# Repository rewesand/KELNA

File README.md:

# KELNA

> [!NOTE]
> **This project is under development.**

Low-frequency noise preamplifier hardware for precision voltage references and Zener diodes, designed for the **0.1–10 Hz** measurement window. Nominal midband gain is **11,400 V/V (≈81.1 dB)**. The prototype uses a split battery supply of **±6.8 to ±8.4 V** and a **high-impedance output load**.

## PCB routing

**Front copper** · [SVG](docs/images/copper-front.svg)

**Back copper** · Underside view with reference overlay · [SVG](docs/images/copper-back.svg)

## Using the input

For the BNC input (J1), set JP1 to **1–2 (INT)**. Select **PRE** before connecting a reference, with positive voltage on the centre pin and return on the shell.

| SW1 position | Signal path |
| --- | --- |
| **PRE — precharge** | Charges C1 (2,200 µF) through R1 (15 kΩ) while isolating the amplifier from the reference's DC step. |
| **MEAS — measure** | Bypasses R1 and AC-couples the reference noise to the amplifier through C1. R3 (10 kΩ) provides the bias return. |

With a low-impedance 7 V reference and a discharged C1, PRE initially draws **0.47 mA**. The nominal time constant is **33 s**. Ideally, C1 charges to within **0.5 mV** of the reference in about **5.3 min**. After switching to MEAS, check that the first stage has headroom at TP1 and that J3 has settled before recording. Return to PRE before changing the reference or powering down.

For an external selector, move the single JP1 shunt to **2–3 (EXT)** and feed J2. This path bypasses C1, SW1 and R3. The selector must provide its own AC coupling, input bias return and precharge.

## Two gain stages

1. **×2,000** — four AD8428 amplifiers in parallel, with the output taken from U1 and AC-coupled to the second stage. [Analog Devices circuit, Figure 1](https://www.analog.com/en/resources/analog-dialogue/articles/low-noise-inamp-nanovolt-sensitivity.html)
2. **×5.7** — OPA2140 non-inverting gain stage (1 kΩ and 4.7 kΩ), followed by a second-order **10 Hz** low-pass filter.

The nominal midband gain is **2,000 × 5.7 = 11,400 V/V**. The two AC couplings have nominal corners near 7 mHz with a low-impedance source on J1. Apply the 0.1 Hz lower limit when analysing the recording.

## Board and connectors

100 × 60 mm, two layers. Connect J3 to a high-impedance input. Power connector J21 uses **1 = +BAT, 2 = battery midpoint / GND, 3 = −BAT**.

## Design files

- [KiCad project](KELNA.kicad_pro), [schematic](KELNA.kicad_sch) and [PCB](KELNA.kicad_pcb)
- [Vector schematic PDF](docs/schematic.pdf)
- [Assembly and mechanical drawings](KELNA-placement.pdf)
- [Copper-layer PDF](KELNA-routing.pdf)
- [Bill of materials](KELNA-BOM.csv) and [DRC report](KELNA-DRC.rpt)
- [Revision 0.14 fabrication archive](fabrication/KELNA-rev0.14-fab.zip)

## Schematic

[Schematic SVG](docs/images/schematic.svg) · [Schematic PDF](docs/schematic.pdf)

Several local footprints use KiCad library land patterns with modified silkscreen or solder access. [KiCad library notice](third_party/KiCad-library-license.md).

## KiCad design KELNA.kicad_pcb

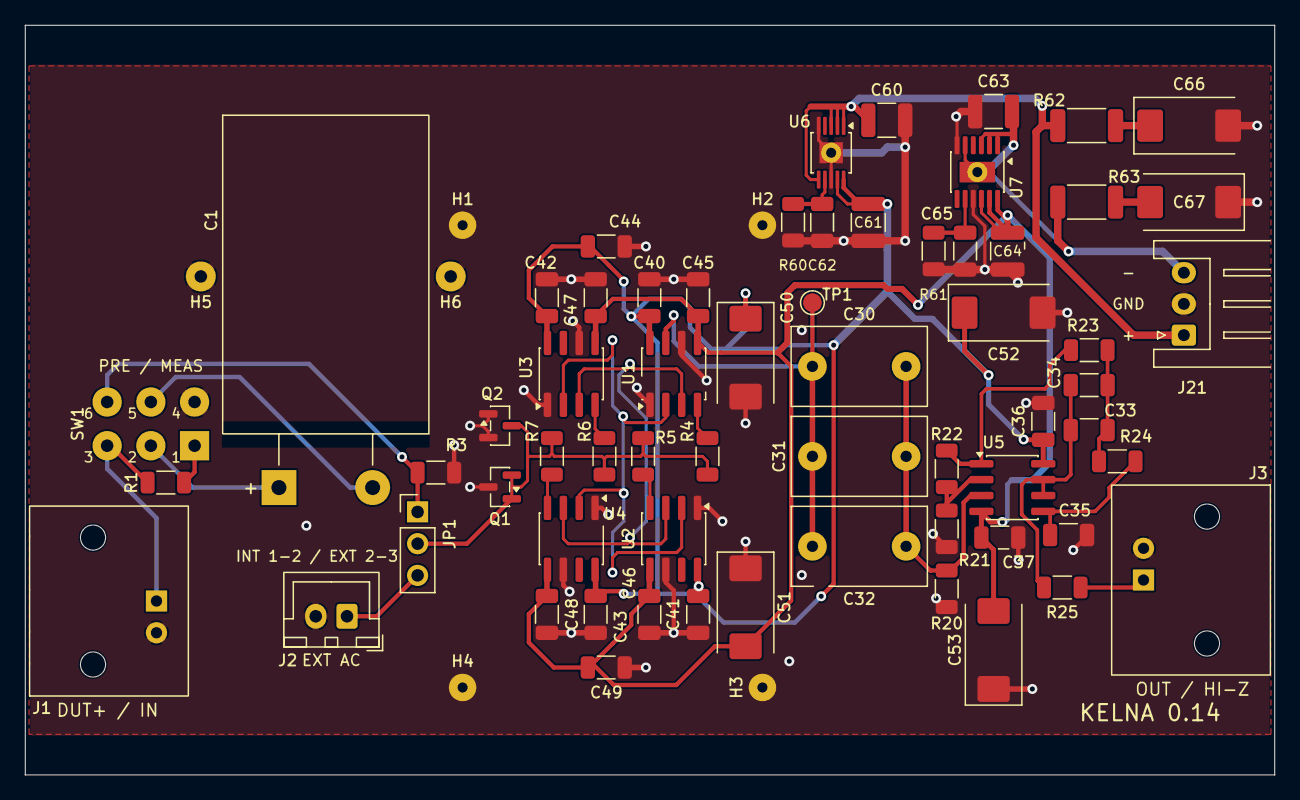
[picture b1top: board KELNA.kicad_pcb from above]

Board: 2 copper layers, 100.0 x 60.0 mm, 69 parts (0 on the bottom side), 30 nets.

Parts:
C1: 2200uF / 16V; CP_Radial_D16mm_L25mm_P7.50mm_Horizontal
C30, C31: 2.2u / 63V PET; C_KEMET_R66_L10.5mm_W6.0mm_P7.50mm
C32: 2.2u / 63V PET; C_KEMET_R66_L10.5mm_W6.0mm_P7.50mm_SilkTrim_C32
C33: 100n C0G; C_1206_3216Metric_SilkTrim_C33
C34, C36, C40, C41, C42, C43, C45, C46, C47, C48: 100n C0G; C_1206_3216Metric
C35: 100n C0G; C_1206_3216Metric_SilkTrim_C35
C37: 100n C0G; C_1206_3216Metric_SilkTrim_C37
C44, C49: 4.7 uF; C_1206_3216Metric
C50, C51, C52, C53, C66, C67: 47u / 16V; CP_EIA-7343-31_Kemet-D
C60, C61, C63: 22u / 25V; C_1210_3225Metric
C62, C65: 4.7u / 25V; C_1206_3216Metric
C64: 22u / 25V; C_1210_3225Metric_SilkTrim_C64
H1, H2, H3, H4: Shield GND; Shield_Post_PTH_D0.8mm
H5, H6: C1 clip GND; Clamp_Anchor_PTH_D1.0mm
J1: BNC DUT IN; BNC_TE_5227161-6_Horizontal
J2: EXT AC IN; JST_XH_B2B-XH-A_1x02_P2.50mm_Vertical
J3: BNC; BNC_TE_5227161-6_Horizontal
J21: BATTERY; JST_XH_S3B-XH-A_1x03_P2.50mm_Horizontal_Panel
JP1: INT / EXT; PinHeader_1x03_P2.54mm_Vertical
Q1, Q2: MMBF4117; SOT-23
R1: 15k; R_1206_3216Metric
R3: 10k; R_1206_3216Metric
R4, R5, R6, R7: 0R; R_1206_3216Metric
R20: 3.3M; R_1206_3216Metric
R21: 1k; R_1206_3216Metric
R22: 4.7k; R_1206_3216Metric
R23, R24: 113k; R_1206_3216Metric
R25: 2.2k; R_1206_3216Metric
R60, R61: 50.0k; R_1206_3216Metric
R62, R63: 0.47R; R_2010_5025Metric
SW1: PRE / MEAS; SW_DPDT_Panel_Wires_2x03_P3.5mm
TP1: PRE_OUT; TestPoint_Pad_D1.5mm
U1: AD8428BRZ; SOIC-8_3.9x4.9mm_P1.27mm_SilkTrim_U1
U2, U3: AD8428BRZ; SOIC-8_3.9x4.9mm_P1.27mm
U4: AD8428BRZ; SOIC-8_3.9x4.9mm_P1.27mm_SilkTrim_U4
U5: OPA2140; SOIC-8_3.9x4.9mm_P1.27mm
U6: LT3042IMSE; MSOP-10-1EP_3x3mm_P0.5mm_EP1.68x1.88mm_BacksideSolder
U7: LT3094EMSE; MSOP-12-1EP_3x4.039mm_P0.65mm_EP1.651x2.845mm_BacksideSolde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

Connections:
/+5VA: C36.1, C40.1, C41.1, C42.1, C43.1, C44.1, C50.1, C52.1, C61.1, U1.8 (V+), U2.8 (V+), U3.8 (V+), U4.8 (V+), U5.8 (V+), U6.9 (OUTS), U6.10 (OUT)
/-5VA: C37.1, C45.1, C46.1, C47.1, C48.1, C49.1, C51.2, C53.2, C64.1, U1.5 (V-), U2.5 (V-), U3.5 (V-), U4.5 (V-), U5.4 (V-), U7.10 (OUTS), U7.11 (OUT), U7.12 (OUT)
/AC_EXTERNAL: J2.1, JP1.3 (B)
/AC_INTERNAL: JP1.1 (A), R3.1, SW1.6 (C)
/DUT_IN: J1.1 (In), R1.1, SW1.3 (C)
/DUT_PRE: R1.2, SW1.1 (A)
/FIL_N: U1.2 (-FIL), U2.2 (-FIL), U3.2 (-FIL), U4.2 (-FIL)
/FIL_P: U1.3 (+FIL), U2.3 (+FIL), U3.3 (+FIL), U4.3 (+FIL)
/INPUT_PLUS: JP1.2 (C), Q1.1 (S), Q1.2 (D), Q2.3 (G), R4.1, R5.1, R6.1, R7.1
/OUT: J3.1 (In), R25.2
/POST_GAIN: R22.2, R23.1, U5.1
/PRE_OUT: C30.1, C31.1, C32.1, TP1.1 (1_1), U1.7 (OUT)
/VN_BAT: C63.1, J21.3, R63.1, U7.1 (IN), U7.2 (IN), U7.3 (EN/UV), U7.5 (PGFB), U7.13 (IN)
/VP_BAT: C60.1, J21.1, R62.1, U6.1 (IN), U6.2 (IN), U6.3 (EN/UV), U6.6 (PGFB)
GND: C35.2, C36.2, C37.2, C40.2, C41.2, C42.2, C43.2, C44.2, C45.2, C46.2, C47.2, C48.2, C49.2, C50.2, C51.1, C52.2, C53.1, C60.2, C61.2, C62.2, C63.2, C64.2, C65.2, C66.2, C67.1, H1.1 (1_1), H2.1 (1_1), H3.1 (1_1), H4.1 (1_1), H5.1 (1_1), H6.1 (1_1), J1.2 (Ext), J2.2, J3.2 (Ext), J21.2, Q1.3 (G), Q2.1 (S), Q2.2 (D), R3.2, R20.2, R21.2, R60.2, R61.2, SW1.4 (A), U1.1 (-IN), U1.6 (REF), U2.1 (-IN), U2.6 (REF), U3.1 (-IN), U3.6 (REF), U4.1 (-IN), U4.6 (REF), U6.5 (ILIM), U6.8 (GND), U6.11 (GND), U7.6 (ILIM), U7.9 (GND)
unnamed: C33.1, C34.1, R23.2, R24.1
unnamed: C66.1, R62.2
unnamed: C67.2, R63.2
unnamed: C1.1, SW1.2 (B)
unnamed: C1.2, SW1.5 (B)
unnamed: R4.2, U1.4 (+IN)
unnamed: R5.2, U2.4 (+IN)
unnamed: R6.2, U3.4 (+IN)
unnamed: R7.2, U4.4 (+IN)
unnamed: C30.2, C31.2, C32.2, R20.1, U5.3 (+)
unnamed: R21.1, R22.1, U5.2 (-)
unnamed: C35.1, R24.2, U5.5 (+)
unnamed: C33.2, C34.2, R25.1, U5.6 (-), U5.7
unnamed: C62.1, R60.1, U6.7 (SET)
unnamed: C65.1, R61.1, U7.8 (SET)

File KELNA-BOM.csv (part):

"Refs / Designator","Value / Description","Manufacturer","MPN","Mouser No","Qty per board or set","Qty to order","Assembly / Variant","Footprint","Mouser DE URL","Observed stock pcs","Stock source locale","Index age at 2026-11-20","Stock status","Stock evidence URL","Other indexed observations","Manufacturer URL","Notes / Примечания"
"C1","2200uF / 16V","Nichicon","UKL1C222MHD","647-UKL1C222MHD","1","1","Вход; электролит установлен лёжа","KELNA:CP_Radial_D16mm_L25mm_P7.50mm_Horizontal","https://www.mouser.de/ProductDetail/Nichicon/UKL1C222MHD","244","DE","crawled yesterday","indexed_in_stock","https://www.mouser.de/de/c/?q=Nichicon+Low+Leakage+Aluminum+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","","https://www.nichicon.co.jp/english/series_items/catalog_pdf/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","2200 мкФ, 16 В; плюс к DUT. Корпус Ø16×25 мм, шаг 7,5 мм; длина до 26,5 мм. Закрепить корпус; проверить утечку и шум при рабочем напряжении. Серия NRND."
"C30,C31,C32","2.2u / 63V PET","KEMET","R66DD4220AA6AJ","80-R66DD4220AA6AJ","3","3","Межкаскадная связь; три конденсатора параллельно","C30,C31 = KELNA:C_KEMET_R66_L10.5mm_W6.0mm_P7.50mm | C32 = KELNA:C_KEMET_R66_L10.5mm_W6.0mm_P7.50mm_SilkTrim_C32","https://www.mouser.de/ProductDetail/KEMET/R66DD4220AA6AJ","340","Mouser IN counterpart","crawled last month","indexed_in_stock","https://www.mouser.in/en/c/passive-components/capacitors/?ca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","384 pcs; DE; age not recorded; https://www.mouser.de/de/ProductDetail/KEMET/R66DD4220AA6AJ?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","https://content.kemet.com/datasheets/KEM_F3102_R66.pdf","PET, 2,2 мкФ ±5%, 63 В; три параллельно дают 6,6 мкФ. Корпус 10,5×6×12 мм, шаг 7,5 мм; неполярный."
"C33,C34,C35,C36,C37,C40,C41,C42,C43,C45,C46,C47,C48","100n C0G","TDK","C3216C0G1H104J160AA","810-C3216C0G1H104J","13","13","На плате; ФНЧ C33-C35 и развязка питания","C33 = KELNA:C_1206_3216Metric_SilkTrim_C33 | C34,C36,C40,C41,C42,C43,C45,C46,C47,C48 = Capacitor_SMD:C_1206_3216Metric | C35 = KELNA:C_1206_3216Metric_SilkTrim_C35 | C37 = KELNA:C_1206_3216Metric_SilkTrim_C37","https://www.mouser.de/ProductDetail/TDK/C3216C0G1H104J160AA","69094","Mouser IL counterpart","crawled 2 days ago","indexed_in_stock","https://www.mouser.co.il/en/ProductDetail/TDK/C3216C0G1H104J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","213641 pcs; DE; crawled 2 months ago; https://www.mouser.de/de/ProductDetail/TDK/C3216C0G1H104J160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","https://product.tdk.com/en/search/capacitor/ceramic/mlcc/inf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","100 нФ ±5%, 50 В, C0G, 1206. C33 и C34 параллельно дают 200 нФ; C35 — 100 нФ. Проверить частоту среза собранного ФНЧ."
"C44,C49,C62,C65","4.7 uF | 4.7u / 25V","TDK","C3216X7R1E475K160AC","810-C3216X7R1E475K","4","4","Питание; фильтрация и развязка","Capacitor_SMD:C_1206_3216Metric","https://www.mouser.de/ProductDetail/TDK/C3216X7R1E475K160AC","81833","EU","crawled 5 days ago","indexed_in_stock","https://eu.mouser.com/en/ProductDetail/TDK/C3216X7R1E475K160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","","https://product.tdk.com/en/search/capacitor/ceramic/mlcc/inf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","4,7 мкФ ±10%, 25 В, X7R, 1206; C62/C65 — развязка SET. Ёмкость зависит от напряжения; избегать механической вибрации."
"C50,C51","47u / 16V","KEMET","T521D476M016ATE045","80-T521D476M16ATE45","2","2","U1-U4; локальная развязка первого каскада","Capacitor_Tantalum_SMD:CP_EIA-7343-31_Kemet-D","https://www.mouser.de/ProductDetail/KEMET/T521D476M016ATE045","125","FR / US counterparts","product crawled last month; matching listing crawled last week","indexed_in_stock","https://www.mouser.fr/fr/ProductDetail/KEMET/T521D476M016ATE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","","https://search.kemet.com/datasheets/KEM_T2076_T52X-530.pdf","47 мкФ, 16 В, полимерный тантал, D; ESR ≤45 мОм. Плюс C50/C52 к +5VA; плюс C51/C53 к GND. Дополнительный bulk; C61/C64 сохраняются."
"C52,C53","47u / 16V","KEMET","T521D476M016ATE045","80-T521D476M16ATE45","2","2","U5; локальная развязка второго каскада","Capacitor_Tantalum_SMD:CP_EIA-7343-31_Kemet-D","https://www.mouser.de/ProductDetail/KEMET/T521D476M016ATE045","125","FR / US counterparts","product crawled last month; matching listing crawled last week","indexed_in_stock","https://www.mouser.fr/fr/ProductDetail/KEMET/T521D476M016ATE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","","https://search.kemet.com/datasheets/KEM_T2076_T52X-530.pdf","47 мкФ, 16 В, полимерный тантал, D; ESR ≤45 мОм. Плюс C50/C52 к +5VA; плюс C51/C53 к GND. Дополнительный bulk; C61/C64 сохраняются."
"C60,C61,C63,C64","22u / 25V","TDK","C3225X7R1E226M250AB","810-C3225X7R1EM250AB","4","4","Питание; фильтрация и развязка","C60,C61,C63 = Capacitor_SMD:C_1210_3225Metric | C64 = KELNA:C_1210_3225Metric_SilkTrim_C64","https://www.mouser.de/ProductDetail/TDK/C3225X7R1E226M250AB","39710","EU","crawled last week","indexed_in_stock","https://eu.mouser.com/en/ProductDetail/TDK/C3225X7R1E226M250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","","https://product.tdk.com/en/search/capacitor/ceramic/mlcc/inf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","22 мкФ ±20%, 25 В, X7R, 1210. По типовому графику: около 21 мкФ при 5 В и 18 мкФ при 8,4 В. Для LT3094 требуется не менее 10 мкФ эффективной ёмкости; типовой график не гарантирует минимум."
"C66,C67","47u / 16V","KEMET","T521D476M016ATE045","80-T521D476M16ATE45","2","2","Питание; фильтрация и развязка","Capacitor_Tantalum_SMD:CP_EIA-7343-31_Kemet-D","https://www.mouser.de/ProductDetail/KEMET/T521D476M016ATE045","125","FR / US counterparts","product crawled last month; matching listing crawled last week","indexed_in_stock","https://www.mouser.fr/fr/ProductDetail/KEMET/T521D476M016ATE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","","https://search.kemet.com/datasheets/KEM_T2076_T52X-530.pdf","47 мкФ, 16 В, полимерный тантал, корпус D; ESR ≤45 мОм. C66: плюс к положительной входной шине; C67: плюс к GND. Соблюдать полярность."
"H1,H2,H3,H4","Shield GND","","","","4","0","Заземлённые стойки экрана; изготовляются на плате","KELNA:Shield_Post_PTH_D0.8mm","","","","","Не закупается / bare PCB","","","","Четыре металлизированные площадки с отверстием 0,8 мм, все подключены к GND; отдельная деталь не требуется."
"H5,H6","C1 clip GND","","","","2","0","Заземлённые отверстия для скобы C1","KELNA:Clamp_Anchor_PTH_D1.0mm","","","","","Не закупается / bare PCB","","","","Шаг 20 мм, отверстия Ø1,0 мм. Одна формованная скоба из лужёной медной проволоки Ø0,6–0,8 мм. Под лежащим C1 разместить отдельную диэлектрическую прокладку поверх маски. Между скобой или фольгой и банкой установить отдельную изоляцию; торцы оставить открытыми. Медная фольга опциональна."
"J1,J3","BNC DUT IN | BNC","TE Connectivity","5227161-6","571-5227161-6","2","2","На плате и панели; угловой BNC","KELNA:BNC_TE_5227161-6_Horizontal","https://www.mouser.de/de/ProductDetail/TE-Connectivity/52271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","3539","DE","1 week","indexed in stock","https://www.mouser.de/de/c/connectors/rf-interconnects/?gend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","","https://www.te.com/en/product-5227161-6.html","Одинарный угловой BNC, 50 Ом. Гайка и стопорная шайба приобретаются отдельно; используется собственный посадочный рисунок TE 5227161-6."
"J1_J3_JAM_NUTS","1-329631-2","TE Connectivity","1-329631-2","571-13296312","2","2","Вне платы: ответная часть или крепёж","","https://www.mouser.de/de/ProductDetail/TE-Connectivity-AMP/1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","104338","ID/IN","1 week","indexed in stock","https://www.mouser.co.id/en/ProductDetail/TE-Connectivity-AM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","","https://www.te.com/commerce/DocumentDelivery/DDEController?A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","Контргайка 1/2-28 для панельного крепления BNC 5227161-6; по одной на J1 и J3."
"J1_J3_LOCKWASHERS","1-329632-2","TE Connectivity","1-329632-2","571-13296322","2","2","Вне платы: ответная часть или крепёж","","https://www.mouser.de/de/ProductDetail/TE-Connectivity-AMP/1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","4904","DE","4 days","indexed in stock","https://www.mouser.de/de/c/?type=Lock+Washer","","https://www.te.com/commerce/DocumentDelivery/DDEController?A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","Стопорная шайба для BNC 5227161-6; по одной на J1 и J3, устанавливается с контргайкой."
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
